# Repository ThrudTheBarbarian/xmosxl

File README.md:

# xmosxl

Experiment on adding a bunch of i/o slots to any given 8-bit (or other!) computer that exposes its bus and allows expansion. The first (only ?) target will be the Atari XL...

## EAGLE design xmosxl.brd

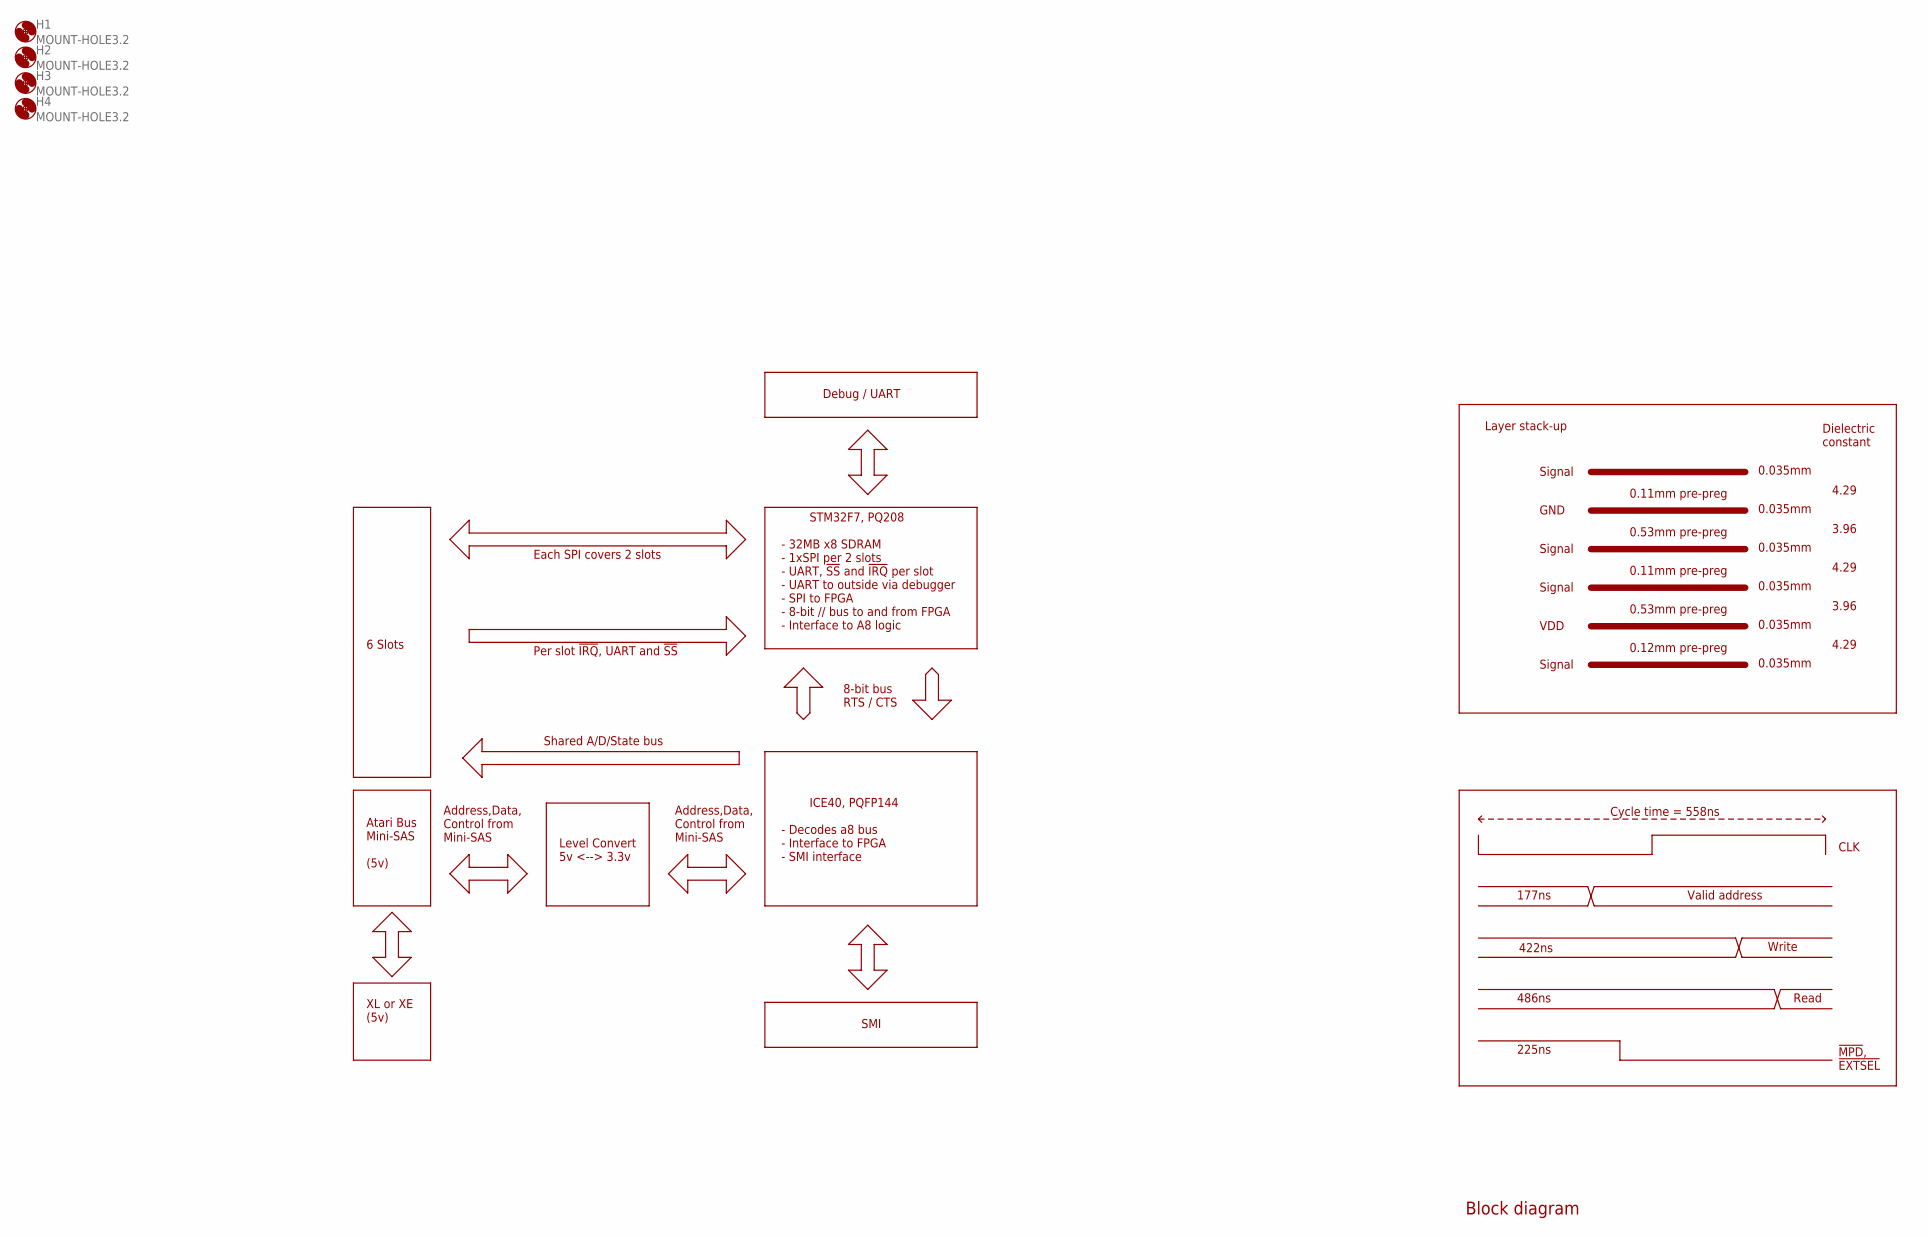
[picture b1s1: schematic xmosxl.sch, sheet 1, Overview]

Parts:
H1, H2, H3, H4: MOUNT-HOLE3.2; 3,2

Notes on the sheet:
Atari Bus Mini-SAS (5v)
Level Convert 5v <--> 3.3v
XL or XE (5v)
STM32F7, PQ208 - 32MB x8 SDRAM - 1xSPI per 2 slots - UART, !SS! and !IRQ! per slot - UART to outside via debugger - SPI to FPGA - 8-bit // bus to and from FPGA - Interface to A8 logic
6 Slots
Each SPI covers 2 slots
Address,Data, Control from Mini-SAS
Shared A/D/State bus
0.53mm pre-preg
0.12mm pre-preg
0.11mm pre-preg
0.035mm
Layer stack-up
GND
Dielectric constant
Cycle time = 558ns
Valid address
Write
Read
177ns
422ns
486ns
225ns
!MPD!, !EXTSEL!
CLK
VDD
Signal
4.29
3.96
Per slot !IRQ!, UART and !SS!
Debug / UART
Block diagram
ICE40, PQFP144 - Decodes a8 bus - Interface to FPGA - SMI interface
SMI
8-bit bus RTS / CTS

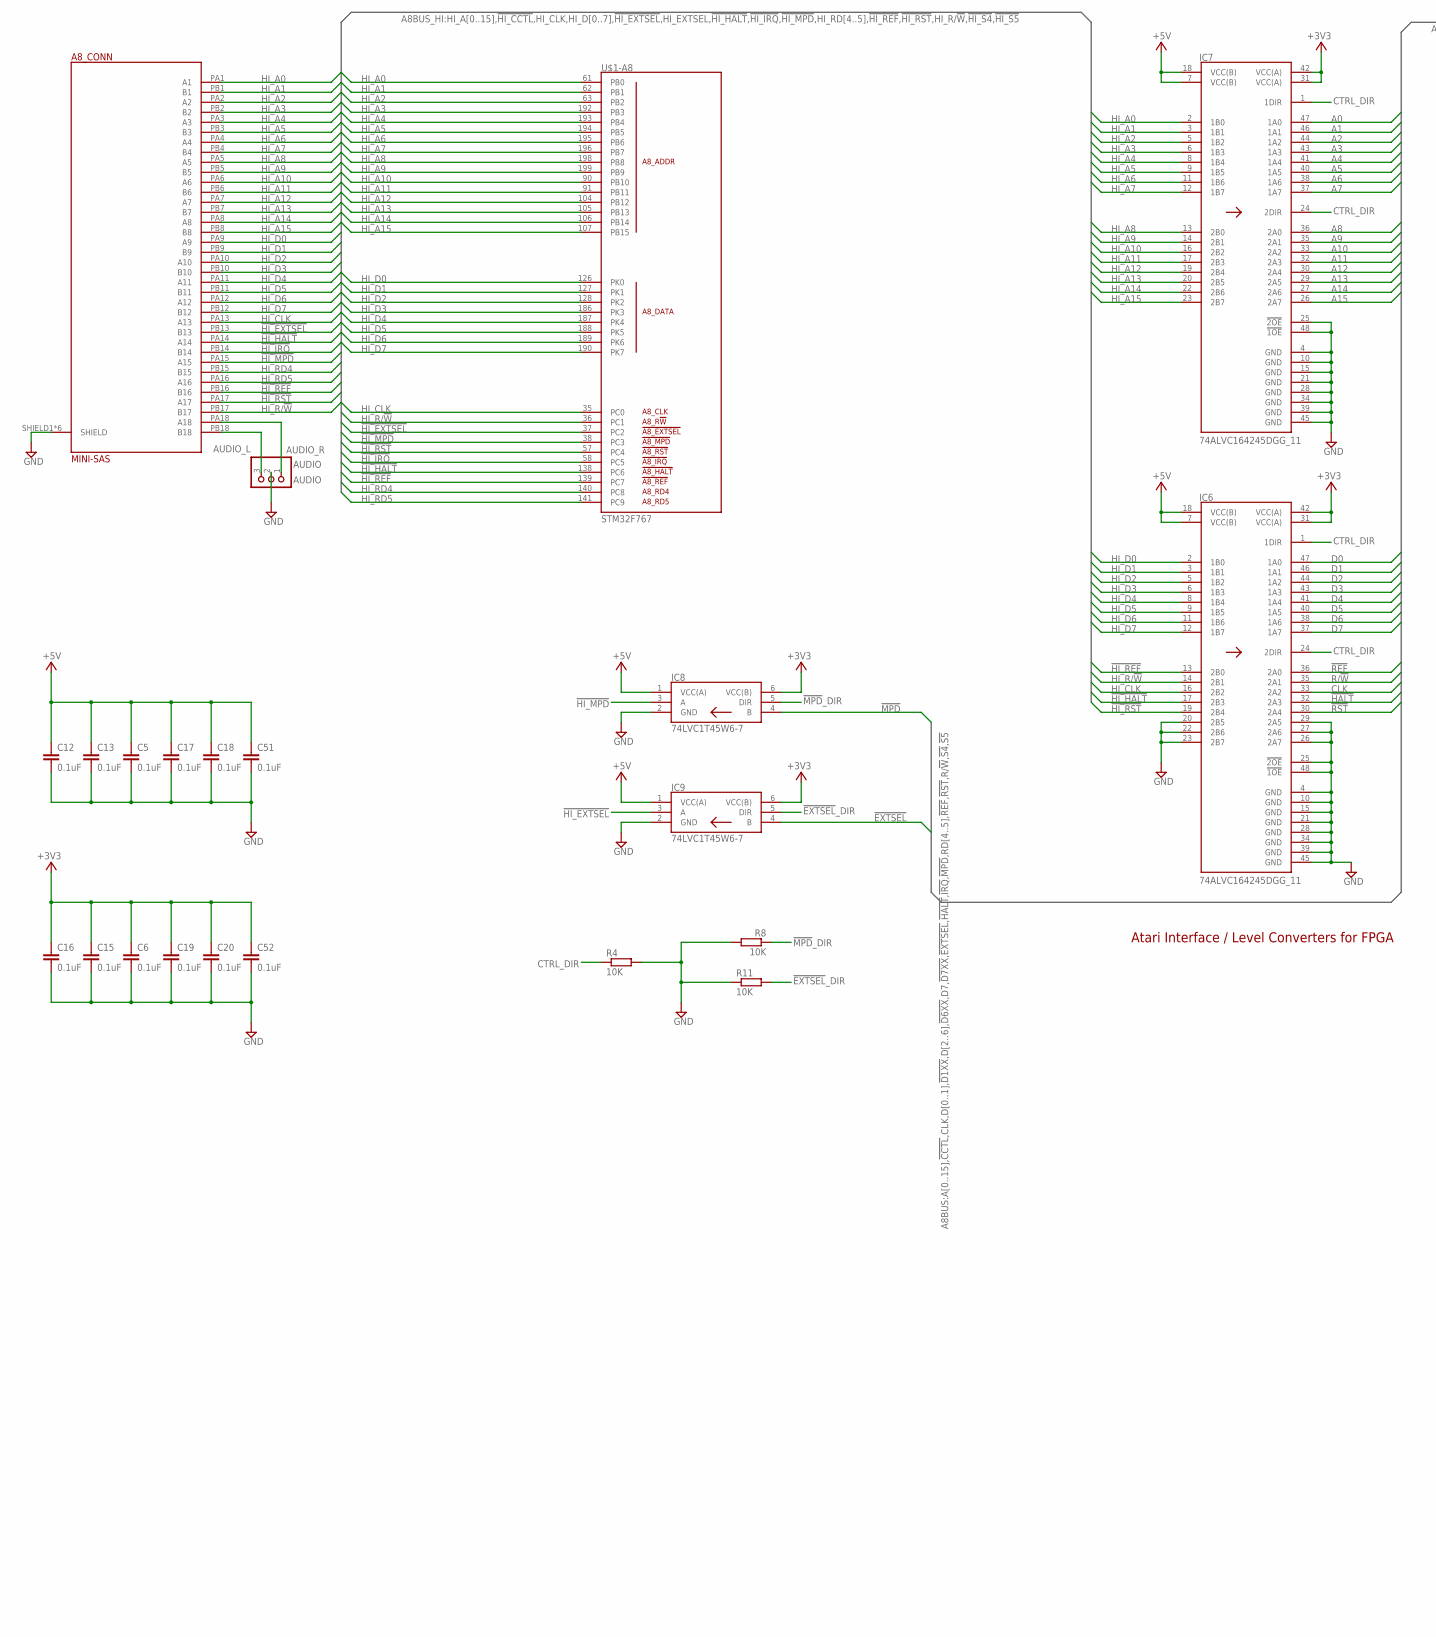
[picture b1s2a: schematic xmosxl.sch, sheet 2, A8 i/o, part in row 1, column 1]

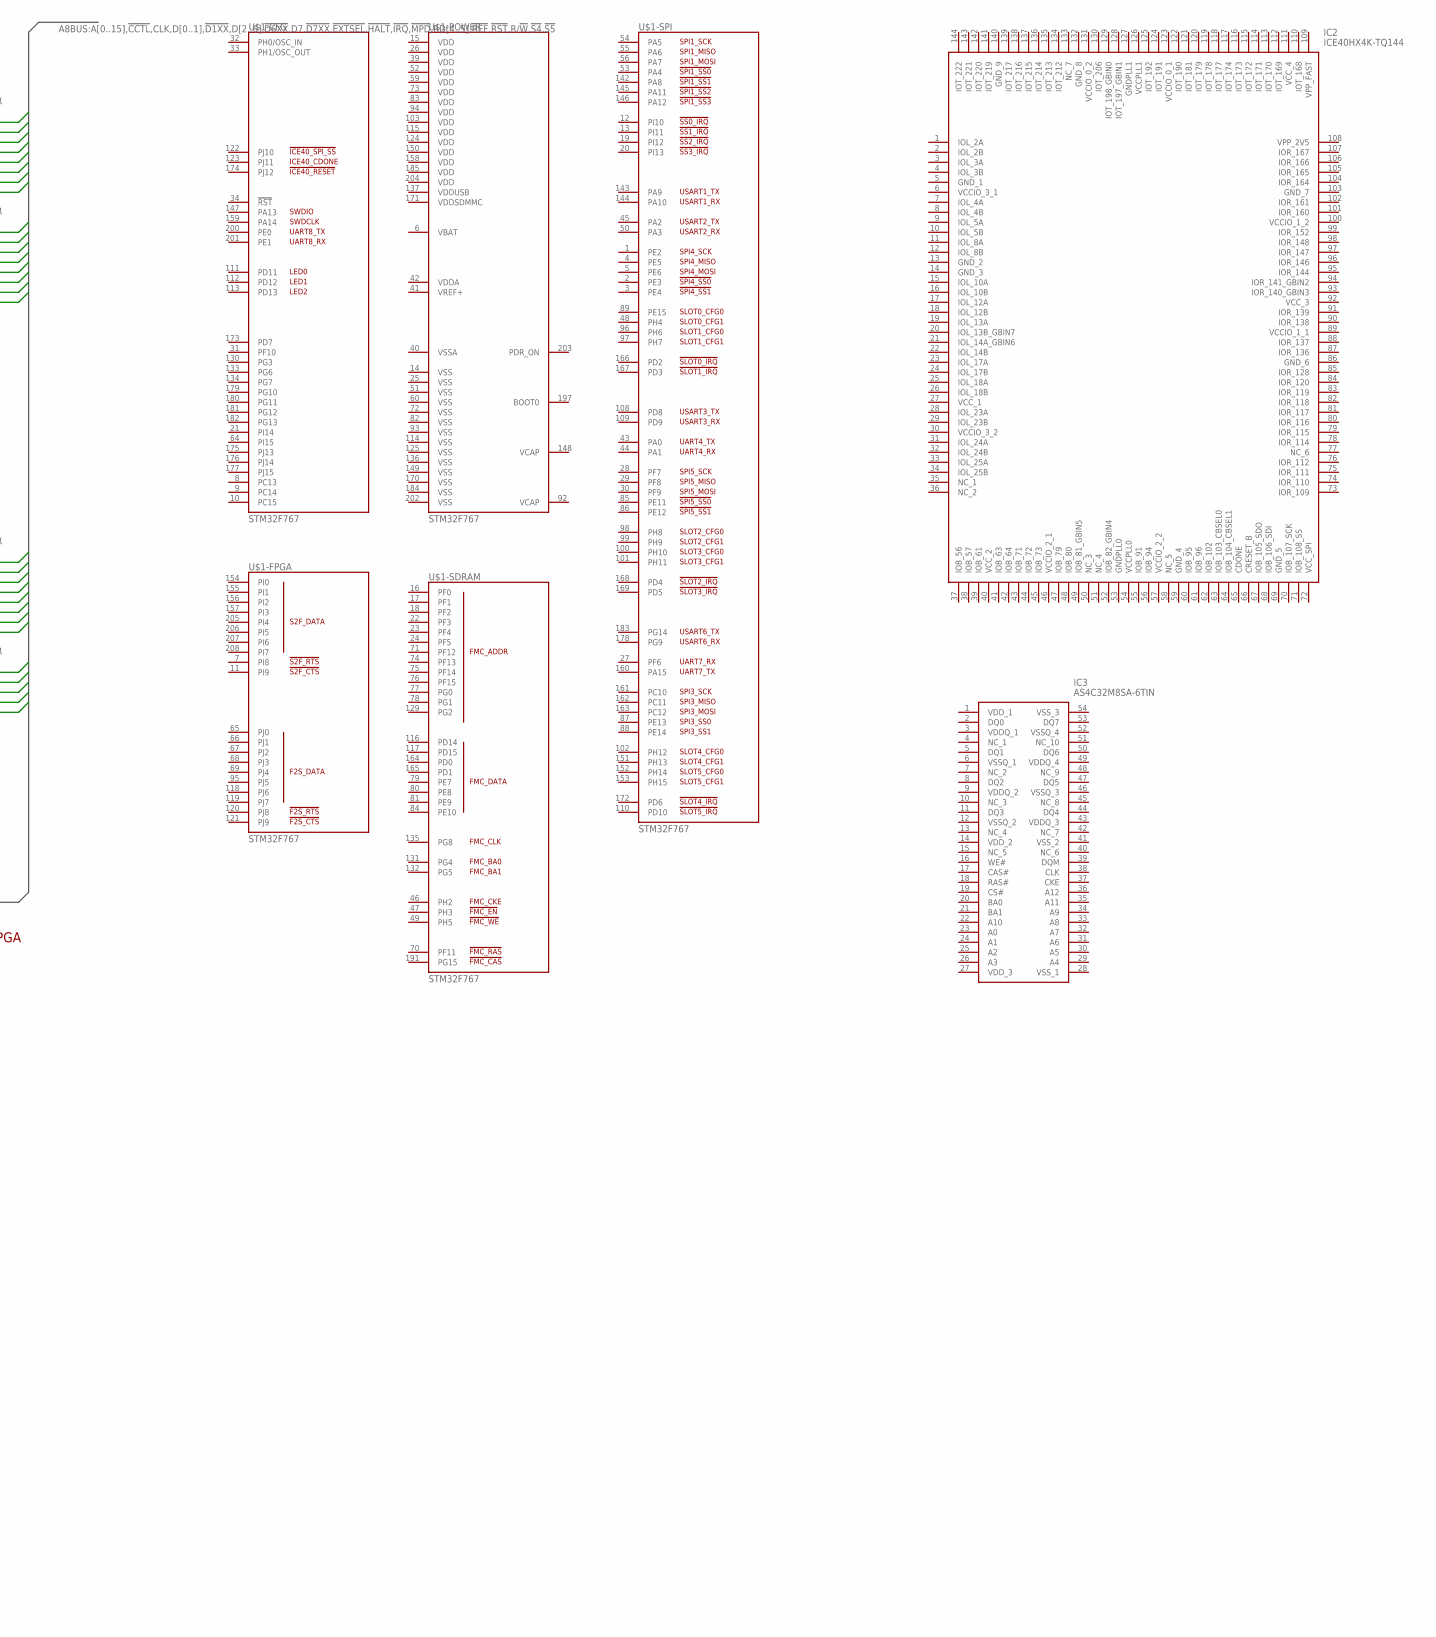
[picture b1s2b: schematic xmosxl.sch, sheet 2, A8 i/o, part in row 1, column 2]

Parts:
A8_CONN: MINI-SAS
AUDIO: AUDIO; 1X03
C5, C6, C12, C13, C15, C16, C17, C18, C19, C20, C51, C52: 0.1uF; C0201
IC2: ICE40HX4K-TQ144; QFP50P2200X2200X160-144N
IC3: AS4C32M8SA-6TIN; SOP80P1176X120-54N
IC6, IC7: 74ALVC164245DGG_11; SOP50P810X120-48N
IC8, IC9: 74LVC1T45W6-7; SOT95P285X140-6N
R4, R8, R11: 10K; R0201
U$1: STM32F767; QFP50P3000X3000X160-208N

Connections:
!EXTSEL!: IC9.4 (B)
!EXTSEL!_DIR: IC9.5 (DIR), R11.2
!HALT!: IC6.32 (2A3)
!HI_EXTSEL!: A8_CONN.PB13 (B13), IC9.3 (A), U$1.37 (PC2)
!HI_HALT!: A8_CONN.PA14 (A14), IC6.17 (2B3), U$1.138 (PC6)
!HI_IRQ!: A8_CONN.PB14 (B14), U$1.58 (PC5)
!HI_MPD!: A8_CONN.PA15 (A15), IC8.3 (A), U$1.38 (PC3)
!HI_REF!: A8_CONN.PB16 (B16), IC6.13 (2B0), U$1.139 (PC7)
!HI_RST!: A8_CONN.PA17 (A17), IC6.19 (2B4), U$1.57 (PC4)
!MPD!: IC8.4 (B)
!MPD!_DIR: IC8.5 (DIR), R8.1
!REF!: IC6.36 (2A0)
!RST!: IC6.30 (2A4)
+3V3: C6.1, C15.1, C16.1, C19.1, C20.1, C52.1, IC6.31 (VCC(A)), IC6.42 (VCC(A)), IC7.31 (VCC(A)), IC7.42 (VCC(A)), IC8.6 (VCC(B)), IC9.6 (VCC(B)); also elsewhere on the board
+5V: C5.1, C12.1, C13.1, C17.1, C18.1, C51.1, IC6.7 (VCC(B)), IC6.18 (VCC(B)), IC7.7 (VCC(B)), IC7.18 (VCC(B)), IC8.1 (VCC(A)), IC9.1 (VCC(A)); also elsewhere on the board
A0: IC7.47 (1A0)
A1: IC7.46 (1A1)
A2: IC7.44 (1A2)
A3: IC7.43 (1A3)
A4: IC7.41 (1A4)
A5: IC7.40 (1A5)
A6: IC7.38 (1A6)
A7: IC7.37 (1A7)
A8: IC7.36 (2A0)
A9: IC7.35 (2A1)
A10: IC7.33 (2A2)
A11: IC7.32 (2A3)
A12: IC7.30 (2A4)
A13: IC7.29 (2A5)
A14: IC7.27 (2A6)
A15: IC7.26 (2A7)
AUDIO_L: A8_CONN.PB18 (B18), AUDIO.3
AUDIO_R: A8_CONN.PA18 (A18), AUDIO.1
CLK: IC6.33 (2A2)
CTRL_DIR: IC6.1 (1DIR), IC6.24 (2DIR), IC7.1 (1DIR), IC7.24 (2DIR), R4.1
D0: IC6.47 (1A0)
D1: IC6.46 (1A1)
D2: IC6.44 (1A2)
D3: IC6.43 (1A3)
D4: IC6.41 (1A4)
D5: IC6.40 (1A5)
D6: IC6.38 (1A6)
D7: IC6.37 (1A7)
GND: A8_CONN.SHIELD1 (SHIELD), A8_CONN.SHIELD2 (SHIELD), A8_CONN.SHIELD3 (SHIELD), A8_CONN.SHIELD4 (SHIELD), A8_CONN.SHIELD5 (SHIELD), A8_CONN.SHIELD6 (SHIELD), AUDIO.2, C5.2, C6.2, C12.2, C13.2, C15.2, C16.2, C17.2, C18.2, C19.2, C20.2, C51.2, C52.2, IC6.4 (GND), IC6.10 (GND), IC6.15 (GND), IC6.20 (2B5), IC6.21 (GND), IC6.22 (2B6), IC6.23 (2B7), IC6.25 (!2OE), IC6.26 (2A7), IC6.27 (2A6), IC6.28 (GND), IC6.29 (2A5), IC6.34 (GND), IC6.39 (GND), IC6.45 (GND), IC6.48 (!1OE), IC7.4 (GND), IC7.10 (GND), IC7.15 (GND), IC7.21 (GND), IC7.25 (!2OE), IC7.28 (GND), IC7.34 (GND), IC7.39 (GND), IC7.45 (GND), IC7.48 (!1OE), IC8.2 (GND), IC9.2 (GND), R4.2, R8.2, R11.1; also elsewhere on the board
HI_A0: A8_CONN.PA1 (A1), IC7.2 (1B0), U$1.61 (PB0)
HI_A1: A8_CONN.PB1 (B1), IC7.3 (1B1), U$1.62 (PB1)
HI_A2: A8_CONN.PA2 (A2), IC7.5 (1B2), U$1.63 (PB2)
HI_A3: A8_CONN.PB2 (B2), IC7.6 (1B3), U$1.192 (PB3)
HI_A4: A8_CONN.PA3 (A3), IC7.8 (1B4), U$1.193 (PB4)
HI_A5: A8_CONN.PB3 (B3), IC7.9 (1B5), U$1.194 (PB5)
HI_A6: A8_CONN.PA4 (A4), IC7.11 (1B6), U$1.195 (PB6)
HI_A7: A8_CONN.PB4 (B4), IC7.12 (1B7), U$1.196 (PB7)
HI_A8: A8_CONN.PA5 (A5), IC7.13 (2B0), U$1.198 (PB8)
HI_A9: A8_CONN.PB5 (B5), IC7.14 (2B1), U$1.199 (PB9)
HI_A10: A8_CONN.PA6 (A6), IC7.16 (2B2), U$1.90 (PB10)
HI_A11: A8_CONN.PB6 (B6), IC7.17 (2B3), U$1.91 (PB11)
HI_A12: A8_CONN.PA7 (A7), IC7.19 (2B4), U$1.104 (PB12)
HI_A13: A8_CONN.PB7 (B7), IC7.20 (2B5), U$1.105 (PB13)
HI_A14: A8_CONN.PA8 (A8), IC7.22 (2B6), U$1.106 (PB14)
HI_A15: A8_CONN.PB8 (B8), IC7.23 (2B7), U$1.107 (PB15)
HI_CLK: A8_CONN.PA13 (A13), IC6.16 (2B2), U$1.35 (PC0)
HI_D0: A8_CONN.PA9 (A9), IC6.2 (1B0), U$1.126 (PK0)
HI_D1: A8_CONN.PB9 (B9), IC6.3 (1B1), U$1.127 (PK1)
HI_D2: A8_CONN.PA10 (A10), IC6.5 (1B2), U$1.128 (PK2)
HI_D3: A8_CONN.PB10 (B10), IC6.6 (1B3), U$1.186 (PK3)
HI_D4: A8_CONN.PA11 (A11), IC6.8 (1B4), U$1.187 (PK4)
HI_D5: A8_CONN.PB11 (B11), IC6.9 (1B5), U$1.188 (PK5)
HI_D6: A8_CONN.PA12 (A12), IC6.11 (1B6), U$1.189 (PK6)
HI_D7: A8_CONN.PB12 (B12), IC6.12 (1B7), U$1.190 (PK7)
HI_R/!W!: A8_CONN.PB17 (B17), IC6.14 (2B1), U$1.36 (PC1)
HI_RD4: A8_CONN.PB15 (B15), U$1.140 (PC8)
HI_RD5: A8_CONN.PA16 (A16), U$1.141 (PC9)
R/!W!: IC6.35 (2A1)
VBAT: U$1.6 (VBAT)
VCAP: U$1.92 (VCAP), U$1.148 (VCAP)
VDD: U$1.15 (VDD), U$1.26 (VDD), U$1.39 (VDD), U$1.52 (VDD), U$1.59 (VDD), U$1.73 (VDD), U$1.83 (VDD), U$1.94 (VDD), U$1.103 (VDD), U$1.115 (VDD), U$1.124 (VDD), U$1.150 (VDD), U$1.158 (VDD), U$1.185 (VDD), U$1.204 (VDD)
VDDA: U$1.42 (VDDA)
VDDSDMMC: U$1.171 (VDDSDMMC)
VDDUSB: U$1.137 (VDDUSB)
VREF+: U$1.41 (VREF+)
VSS: U$1.14 (VSS), U$1.25 (VSS), U$1.51 (VSS), U$1.60 (VSS), U$1.72 (VSS), U$1.82 (VSS), U$1.93 (VSS), U$1.114 (VSS), U$1.125 (VSS), U$1.136 (VSS), U$1.149 (VSS), U$1.170 (VSS), U$1.184 (VSS), U$1.202 (VSS)
VSSA: U$1.40 (VSSA)

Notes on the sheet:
Atari Interface / Level Converters for FPGA

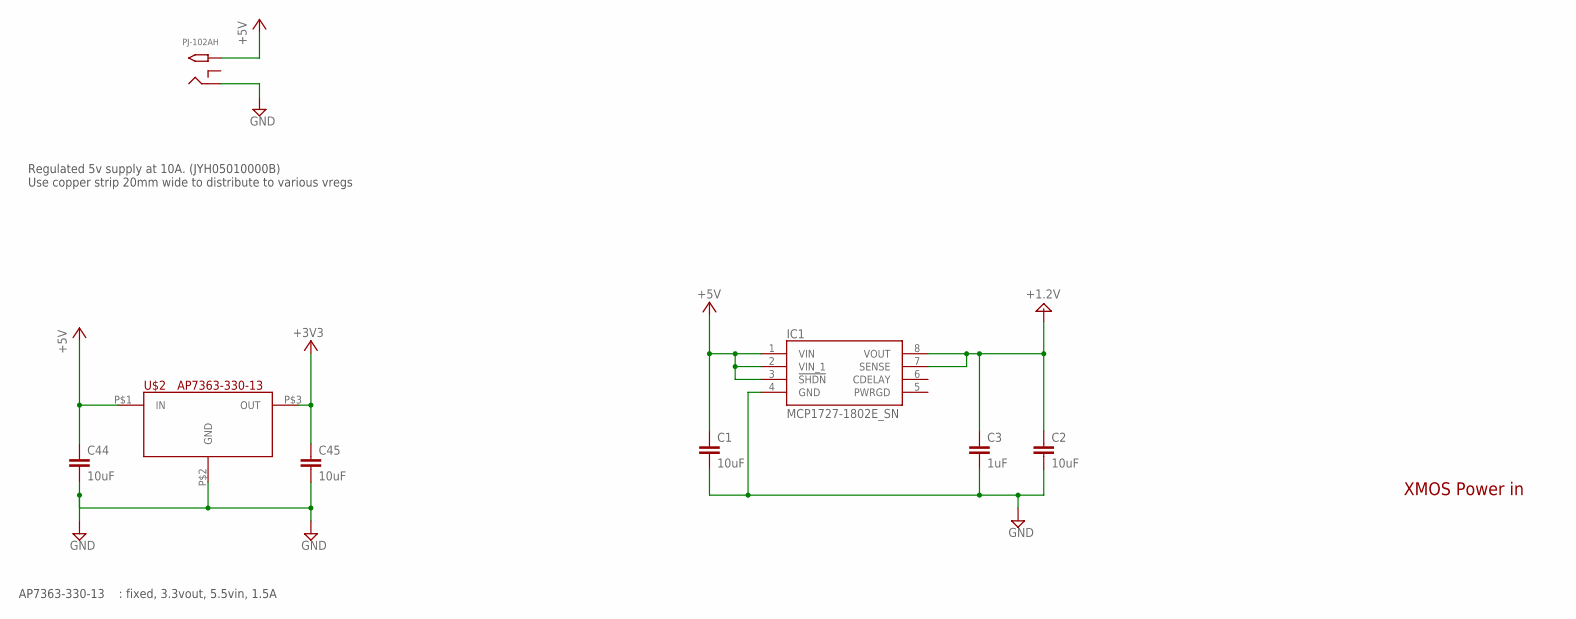
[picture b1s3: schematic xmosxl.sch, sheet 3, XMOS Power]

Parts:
C1, C2, C44, C45: 10uF; C0402K
C3: 1uF; C0201
IC1: MCP1727-1802E_SN; SOIC127P600X175-8N
PJ-102AH: PJ-102AH; PJ-102A
U$2: AP7363-330-13; TO252-3L

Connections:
+1.2V: C2.1, C3.1, IC1.7 (SENSE), IC1.8 (VOUT)
+3V3: C45.1, U$2.P$3 (OUT); also elsewhere on the board
+5V: C1.1, C44.1, IC1.1 (VIN), IC1.2 (VIN_1), IC1.3 (!SHDN), PJ-102AH.TIP, U$2.P$1 (IN); also elsewhere on the board
GND: C1.2, C2.2, C3.2, C44.2, C45.2, IC1.4 (GND), PJ-102AH.RING, U$2.P$2 (GND); also elsewhere on the board

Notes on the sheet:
AP7363-330-13 : fixed, 3.3vout, 5.5vin, 1.5A
Regulated 5v supply at 10A. (JYH05010000B) Use copper strip 20mm wide to distribute to various vregs
XMOS Power in

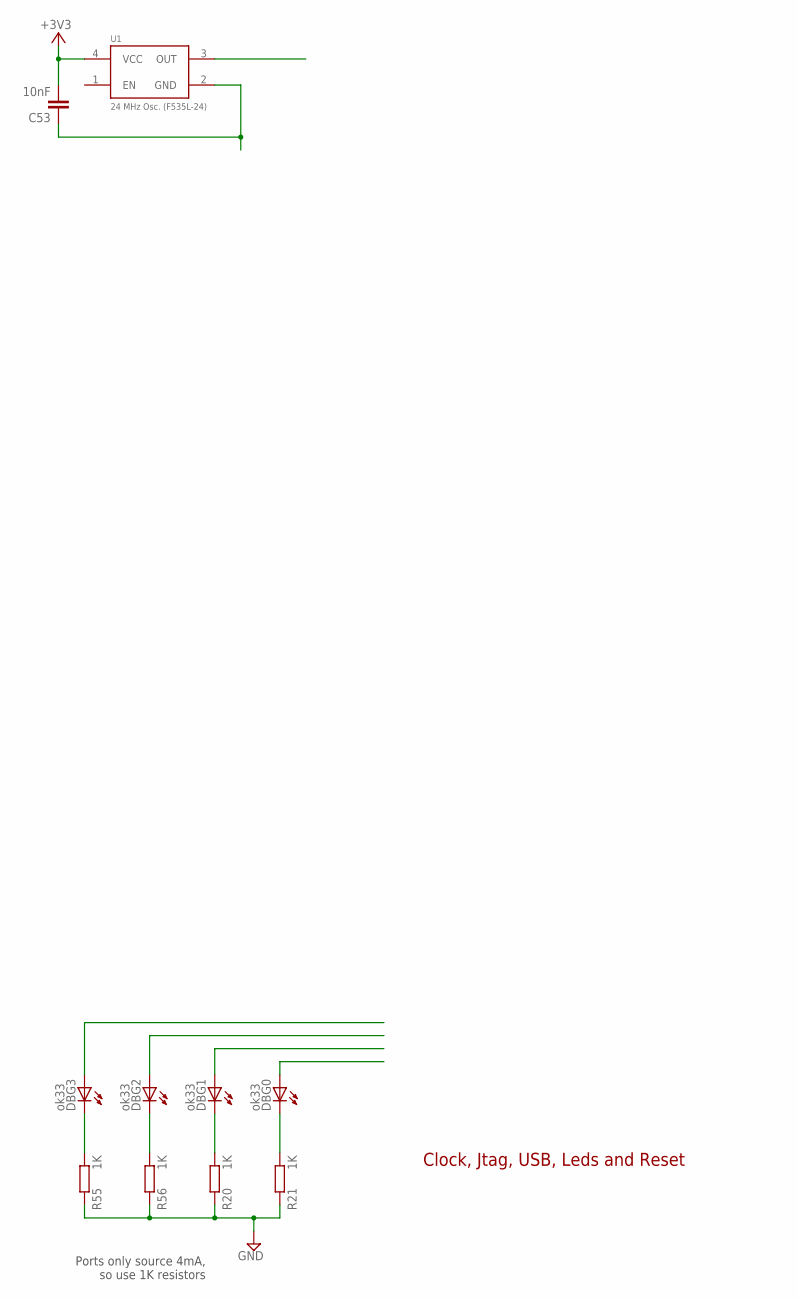
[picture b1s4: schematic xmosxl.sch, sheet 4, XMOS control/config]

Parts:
C53: 10nF; C0201
DBG0, DBG1, DBG2, DBG3: ok33; CHIP-LED0603
R20, R21, R55, R56: 1K; R0201
U1: 24 MHz Osc. (F535L-24); CRYSTAL-OSC-SMD-5X3

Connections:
+3V3: C53.2, U1.4 (VCC); also elsewhere on the board
GND: R20.1, R21.1, R55.1, R56.1; also elsewhere on the board
unnamed: DBG2.C, R56.2
unnamed: DBG0.C, R21.2
unnamed: DBG3.C, R55.2
unnamed: DBG1.C, R20.2
unnamed: C53.1, U1.2 (GND)

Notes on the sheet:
Ports only source 4mA, so use 1K resistors
Clock, Jtag, USB, Leds and Reset

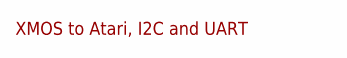
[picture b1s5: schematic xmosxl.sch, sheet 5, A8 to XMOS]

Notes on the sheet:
XMOS to Atari, I2C and UART

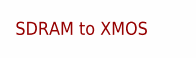
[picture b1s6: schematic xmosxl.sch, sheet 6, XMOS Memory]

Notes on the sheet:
SDRAM to XMOS

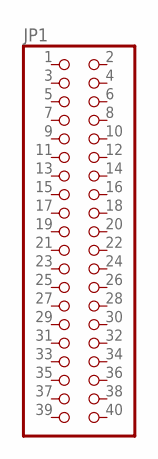
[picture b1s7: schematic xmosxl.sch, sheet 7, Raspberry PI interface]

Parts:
JP1: PINHD-2X20; 2X20

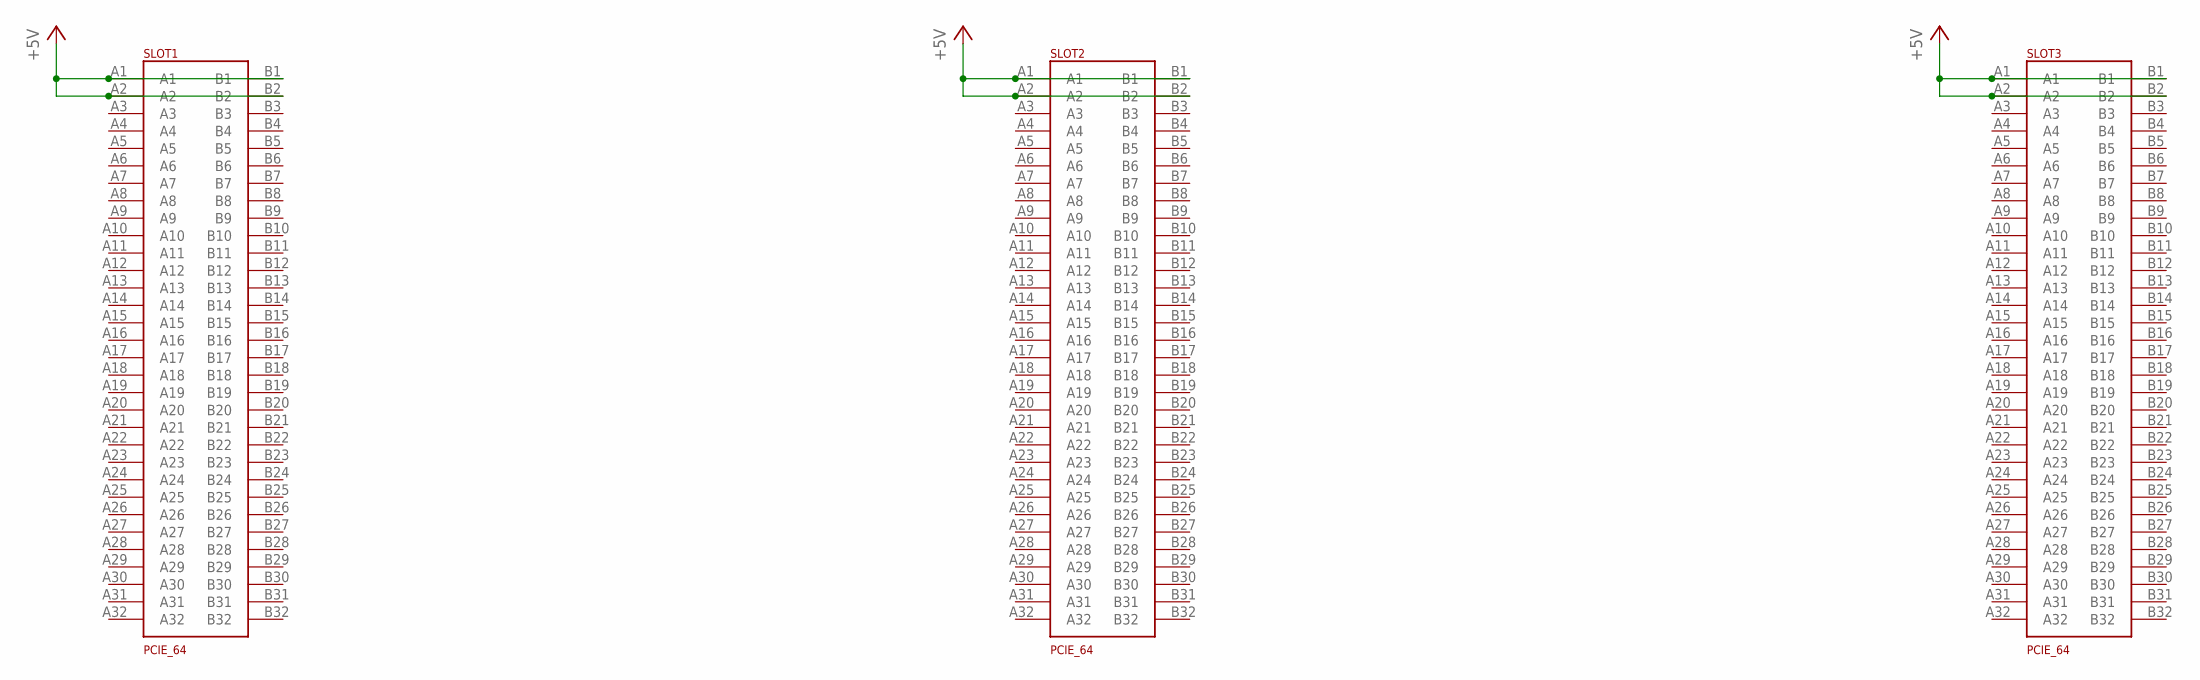
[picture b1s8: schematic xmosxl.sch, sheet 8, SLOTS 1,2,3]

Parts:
SLOT1, SLOT2, SLOT3: PCIE_64; PCI-E_64

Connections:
+5V: SLOT1.A1, SLOT1.A2, SLOT1.B1, SLOT1.B2, SLOT2.A1, SLOT2.A2, SLOT2.B1, SLOT2.B2, SLOT3.A1, SLOT3.A2, SLOT3.B1, SLOT3.B2; also elsewhere on the board

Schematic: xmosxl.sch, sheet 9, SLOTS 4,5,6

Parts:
SLOT4, SLOT5, SLOT6: PCIE_64; PCI-E_64

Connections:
+5V: SLOT4.A1, SLOT4.A2, SLOT4.B1, SLOT4.B2, SLOT5.A1, SLOT5.A2, SLOT5.B1, SLOT5.B2, SLOT6.A1, SLOT6.A2, SLOT6.B1, SLOT6.B2; also elsewhere on the board

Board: 6 copper layers, 53 parts (0 on the bottom side), 51 nets, no tracks yet.

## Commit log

2020-10-22 Initial commit, create a project-specific library and add the XMOS part
2020-10-22 Just test the .gitignore for eagle files
2020-10-22 Add the block diagram
2020-10-22 Start to lay out the design. Add slots and holes to take up space, and start to populate the level converters / vregs
2020-10-22 Add the SDRAM and start on JTAG
2020-10-23 Get rid of files that kill gitX
2020-10-23 Remove a slot - left with 5. Can add an “expansion box” for the remaining 5.
    Add the JTAG link.
2020-10-23 Start work on the slots
2020-10-23 No idea where these came from…
2020-10-23 Add the USB RTUNE resistors - per XMOS, no more other connections need to be made to the USB ports.
2020-10-24 Add the links
2020-10-24 Dd the link resistors
2020-10-24 Board circuit-complete. Decided to ditch the SPI expansion.
    Need to set signal classes and routing hints
2020-10-24 Add some power rail stuff
2020-10-29 Start adding the STM32
2020-10-29 More work on the STM layout
2020-10-30 Dissociate the STM part
2020-10-30 Complete the STM32 part
2020-10-30 Start reconfiguring for STM
2020-10-30 Add the FPGA
2020-10-30 Add the DRAM chip. We now have basically all the major parts on the board. Plenty of space :)

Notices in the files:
parts and their libraries:
SparkFun: Licensing: CC v3.0 Share-Alike You are welcome to use this library for commercial purposes.
